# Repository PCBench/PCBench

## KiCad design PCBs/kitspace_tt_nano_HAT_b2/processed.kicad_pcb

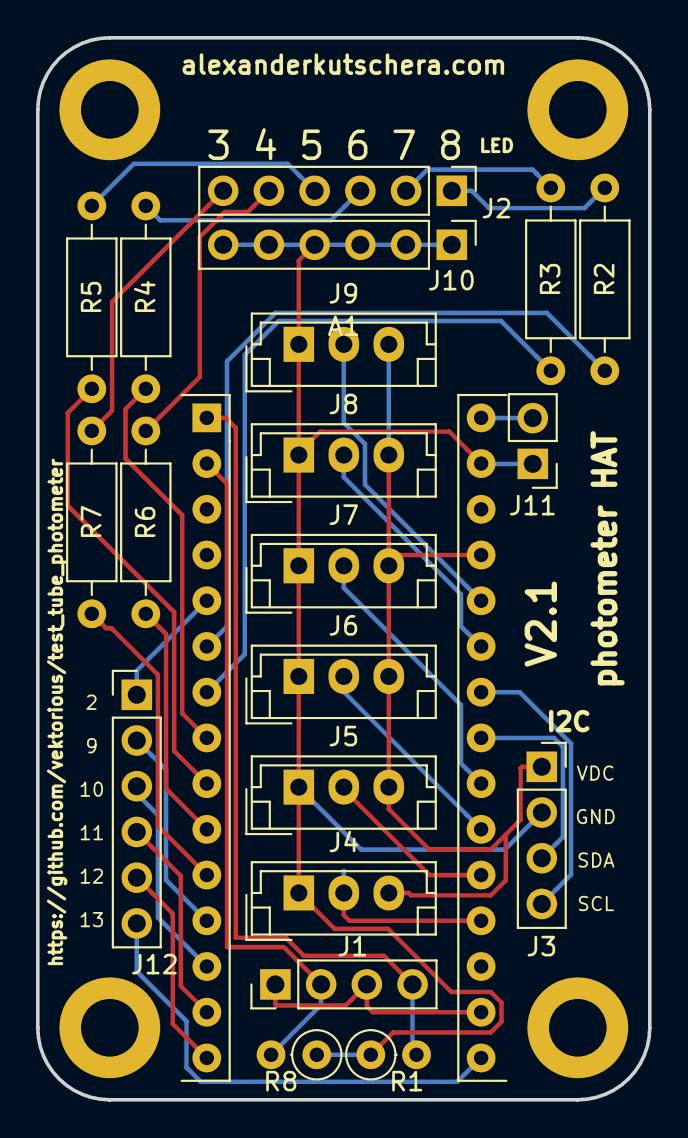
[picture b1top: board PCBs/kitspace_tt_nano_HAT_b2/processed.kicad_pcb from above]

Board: 2 copper layers, 34.0 x 59.0 mm, 21 parts (0 on the bottom side), 32 nets.

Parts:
A1: Arduino_Nano_v3.x; Arduino_Nano2
J1: Conn_01x04_Male; PinHeader_1x04_P2.54mm_Vertical
J2, J10, J12: Conn_01x06_Male; PinHeader_1x06_P2.54mm_Vertical
J3: Conn_01x04_Female; PinSocket_1x04_P2.54mm_Vertical
J4, J5, J6, J7, J8, J9: Conn_01x03_Male; JST_EH_B03B-EH-A_1x03_P2.50mm_Vertical
J11: Conn_01x02_Male; PinHeader_1x02_P2.54mm_Vertical
R1, R8: R; R_Axial_DIN0207_L6.3mm_D2.5mm_P2.54mm_Vertical
R2, R3, R4, R5, R6, R7: R; R_Axial_DIN0207_L6.3mm_D2.5mm_P10.16mm_Horizontal

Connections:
GND: A1.29, J3.2, J4.1, J5.1, J6.1, J7.1, J8.1, J9.1, J10.1, J10.2, J10.3, J10.4, J10.5, J10.6, J11.1, R1.1, R8.1
unnamed: A1.1, J1.4, R1.2
unnamed: A1.2, J1.2, R8.2
unnamed: A1.5, J12.1
unnamed: A1.6, R2.1
unnamed: A1.7, R3.1
unnamed: A1.8, R4.1
unnamed: A1.9, R5.1
unnamed: A1.10, R6.1
unnamed: A1.11, R7.1
unnamed: A1.12, J12.2
unnamed: A1.13, J12.3
unnamed: A1.14, J12.4
unnamed: A1.15, J12.5
unnamed: A1.16, J12.6
unnamed: A1.17, J1.1, J1.3
unnamed: A1.19, J4.2
unnamed: A1.20, J5.2
unnamed: A1.21, J6.2
unnamed: A1.22, J7.2
unnamed: A1.23, J3.3
unnamed: A1.24, J3.4
unnamed: A1.25, J8.2
unnamed: A1.26, J9.2
unnamed: A1.27, J3.1, J4.3, J5.3, J6.3, J7.3, J8.3, J9.3
unnamed: A1.30, J11.2
unnamed: J2.1, R2.2
unnamed: J2.2, R3.2
unnamed: J2.3, R4.2
unnamed: J2.4, R5.2
unnamed: J2.5, R6.2
unnamed: J2.6, R7.2

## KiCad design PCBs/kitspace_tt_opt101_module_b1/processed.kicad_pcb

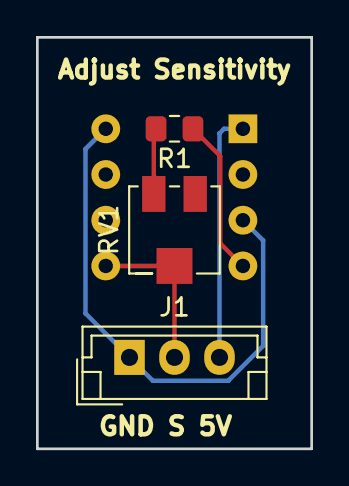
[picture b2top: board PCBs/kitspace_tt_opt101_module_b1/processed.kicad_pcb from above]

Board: 2 copper layers, 15.2 x 22.9 mm, 4 parts (1 on the bottom side), 5 nets.

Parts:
J1: Conn_01x03_Male; JST_EH_B03B-EH-A_1x03_P2.50mm_Vertical
O1: opt101; DIP-8_W7.62mm
R1: R; R_0805_2012Metric_Pad1.15x1.40mm_HandSolder
RV1: R_POT; Potentiometer_Bourns_3214J_Horizontal

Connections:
+5V: J1.3, O1.1
GND: J1.1, O1.3, O1.8
unnamed: J1.2, O1.5, RV1.2
unnamed: O1.4, R1.1
unnamed: R1.2, RV1.1

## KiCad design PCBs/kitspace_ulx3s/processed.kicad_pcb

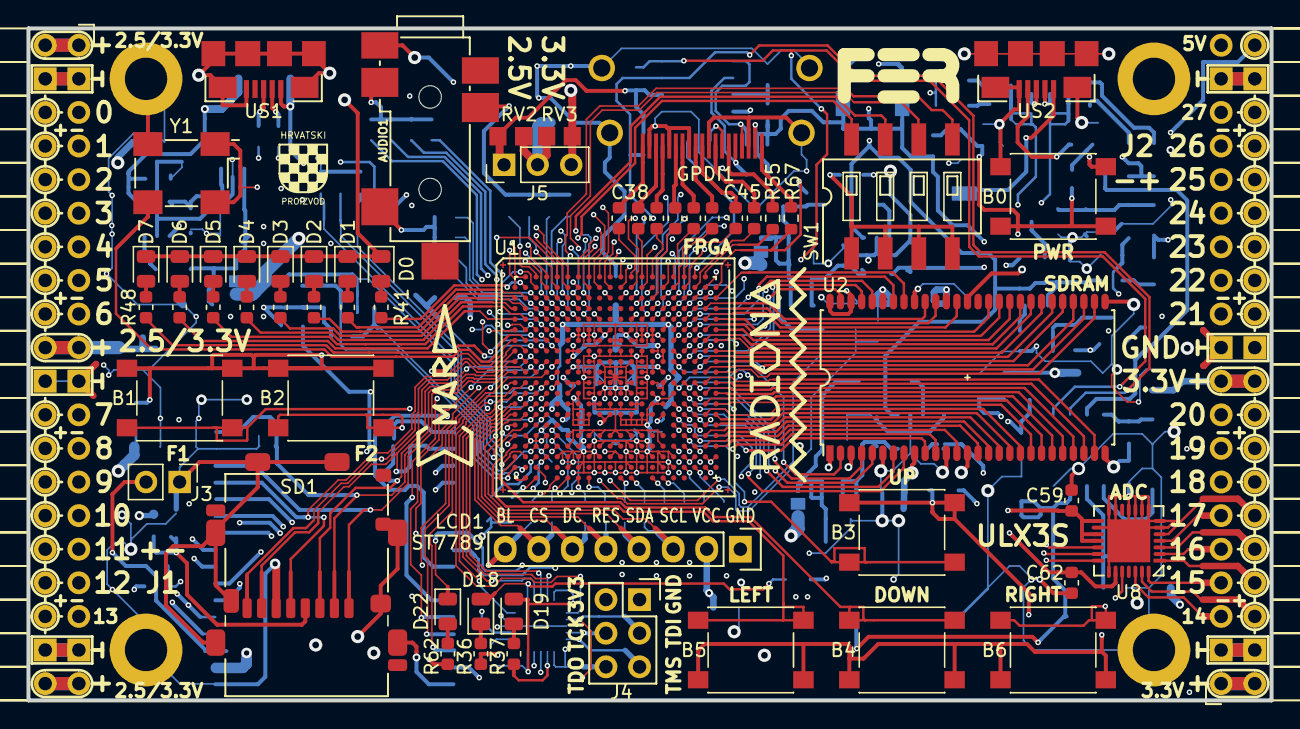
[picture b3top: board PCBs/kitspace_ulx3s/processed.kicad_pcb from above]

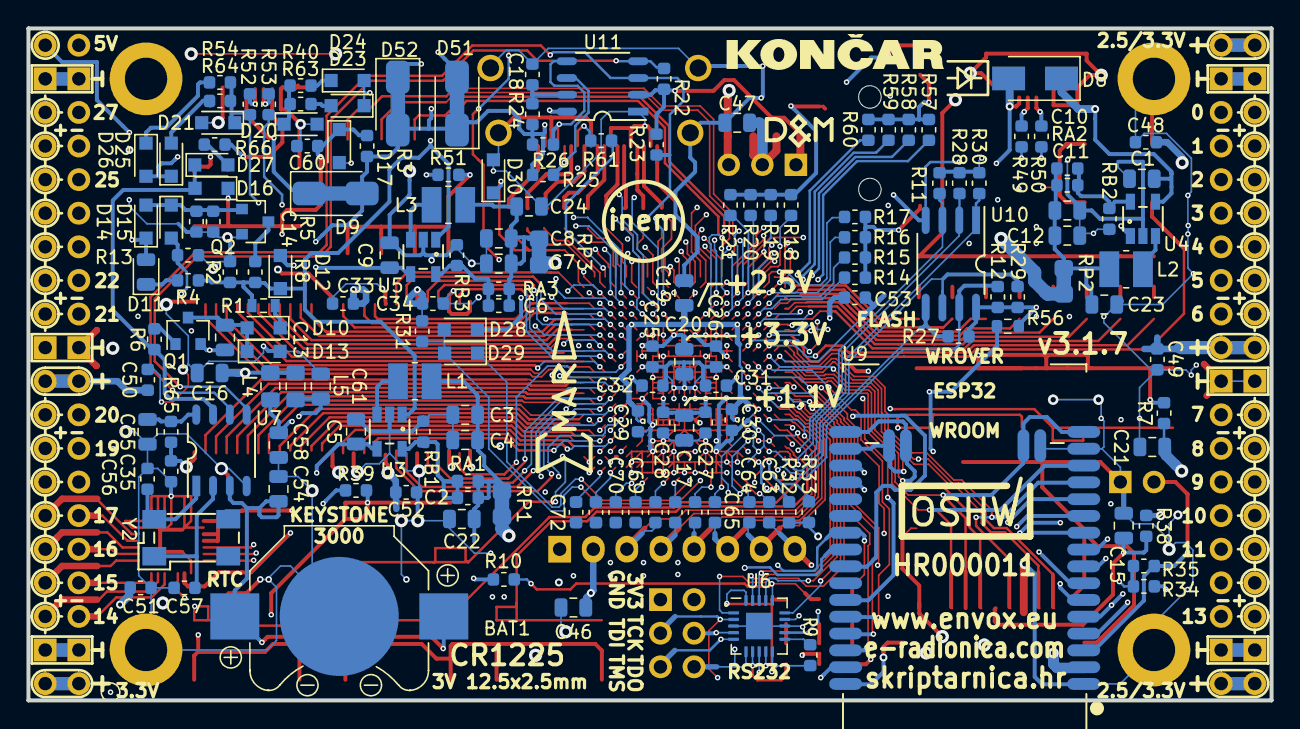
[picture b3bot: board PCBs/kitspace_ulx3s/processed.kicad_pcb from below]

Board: 4 copper layers, 94.0 x 50.8 mm, 234 parts (167 on the bottom side), 287 nets.

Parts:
AE1: 433MHz; TestPoint_Pad_D1.0mm
AUDIO1: JACK_TRS_6PINS; CUI_SJ-43516-SMT
B0, B1, B2, B3, B4, B5, B6: PTS645; SW_SPST_PTS645
BAT1: CR1225; Keystone_3000_1x12mm-CoinCell
C1, C3, C4, C5, C7, C8, C9, C11, C12, C15, C21, C54, C55, C58, C61: 22uF; C_0805_2012Metric
C2, C6, C10, C18: 100pF; C_0603_1608Metric
C13, C16, C17, C19, C20, C22, C23, C24, C46, C47: 2.2uF; C_0805_2012Metric
C14, C59, C60, C62: 220nF; C_0603_1608Metric
C25, C26, C27, C28, C29, C30, C31, C32, C33, C34, C35, C38, C39, C40, C41, C42, C43, C44, C45, C48, C49, C50, C51, C52, C53, C63, C64, C65, C66, C67, C68, C69, C70, C71, C72: 22nF; C_0603_1608Metric
C56, C57: 4.7pF; C_0603_1608Metric
D0, D4, D11, D19: RED; LED_0805_2012Metric
D1, D5: ORANGE; LED_0805_2012Metric
D2, D6, D18: GREEN; LED_0805_2012Metric
D3, D7, D22: BLUE; LED_0805_2012Metric
D8: STPS2L40AF; D_SMA
D9, D51, D52: 0; D_SMA_Jumper_NC
D10, D13, D14, D16, D17, D23, D24, D25, D26, D27, D28, D29: 1N914; D_SOD-323_HandSoldering
D12, D15: BAT54W; D_SOD-323_HandSoldering
D20, D21, D30: 3.6V; D_SOD-323_HandSoldering
D&M: dm2mm
EMARD: emard12mm
EMARD#2: emard12mm
GPDI1: GPDI-D; CONN-10029449-111RLF
H1, H2, H3, H4: HOLE; MountingHole_3.2mm_M3_ISO14580_Pad
HR: HR; hrvatski
J1, J2: CONN_02X20; Socket_Strip_Angled_2x20
J3: WIFI_OFF; PinHeader_1x02_P2.54mm_Vertical
J4: CONN_02X03; Socket_Strip_Straight_2x03
J5: VJ1; PinHeader_1x03_P2.54mm_Vertical
L1, L2, L3: 2.2uH; L_1008_1210
L4, L5: 33uH; L_0805_2012Metric_Pad1.15x1.40mm_HandSolder
LCD1: ST7789; st7789
OSHW: OSHW2mm; oshw
Q1: BC857; SOT-23
Q2: 2N7002; SOT-23
R1, R3, R4, R25, R26, R30: 4.7k; R_0603_1608Metric
R2: 18k; R_0603_1608Metric
R5: 2.2M; R_0603_1608Metric
R6, R8, R14, R18, R29, R40, R54, R57, R66: 1.1k; R_0603_1608Metric
R7, R10, R17, R21, R39, R51, R60: 130; R_0603_1608Metric
R9, R13, R31, R32, R33, R34, R56, R63, R64: 15k; R_0603_1608Metric
R11, R12, R27, R28, R55: 10k; R_0603_1608Metric
R15, R19, R35, R36, R37, R41, R42, R43, R44, R45, R46, R47, R48, R58, R61, R62, R65, R67: 549; R_0603_1608Metric
R16, R20, R59: 270; R_0603_1608Metric
R22, R23: 3.3k; R_0603_1608Metric
R24: 100k; R_0603_1608Metric
R38: 0.47; R_0603_1608Metric
R49, R50, R52, R53: 27; R_0603_1608Metric
RA1, RA2, RA3: 15k; R_0603_1608Metric
RB1: 18k; R_0603_1608Metric
RB2: 4.7k; R_0603_1608Metric
RB3: 3.3k; R_0603_1608Metric
RP1, RP2, RP3: 0; R_0805_2012Metric_Pad1.29x1.40mm_HandSolder_Jumper_NC
RV2, RV3: 0; R_0805_2012Metric_Pad1.29x1.40mm_HandSolder
SD1: 104031-0811; SCHD3A100-104031-0811
SW1: SW_DIP_x04; SW_DIP_x4_W8.61mm_Slide_LowProfile
U1: LFE5U-85F-6BG381C; BGA-381_pitch0.8mm_dia0.4mm
U2: MT48LC16M16A2TG; TSOP54
U3, U4, U5: TLV62569DBV; TSOT-25
U6: FT231XQ; FT231X-QFN-20-1EP_4x4mm_P0.5mm_EP2x2mm
U7: MCP7940NT; SOT96-1
U8: MAX11125; MAX1112x-TQFN-28-1EP_5x5mm_Pitch0.5mm
U9: ESP32
U10: IS25LP128F-JBLE; SOA008-150-208mil
U11: PCA9306D; SM8
US1, US2: MICRO_USB; USB-MICRO-B-FCI-10118192-0001LF
Y1: FNETHE025; Crystal_SMD_7050_4Pads
Y2: 32768Hz; Crystal_SMD_ABS07
fer: fer; fer4mm6
koncar: koncar
radiona: radiona

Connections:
2V5_3V3: C26.1, C47.1, C48.1, C49.1, C53.1, J1.1, J1.2, J1.19, J1.20, J1.39, J1.40, J5.2, R51.1, RV2.2, RV3.1, U1.F9, U1.F10, U1.H6, U1.H7, U1.J6
+1V1: C17.1, C27.1, C28.1, RP1.2, U1.H8, U1.H9, U1.H10, U1.H11, U1.H12, U1.H13, U1.J8, U1.J13, U1.K8, U1.K13, U1.L8, U1.L13, U1.M8, U1.M13, U1.N8, U1.N9, U1.N10, U1.N11, U1.N12, U1.N13, U1.T6, U1.T7, U1.T8, U1.T9, U1.T10, U1.T11, U1.T12, U1.T13, U1.T14, U1.T15, U1.U6, U1.U15
+2V5: C19.1, C29.1, C30.1, J5.1, R22.1, R23.1, RP2.2, RV2.1, U1.F6, U1.F15, U1.P6, U1.P15, U1.V10, U1.V11, U1.V17, U1.V18, U11.2
+3V3: C16.1, C20.1, C21.1, C25.1, C31.1, C32.1, C33.1, C34.1, C35.1, C46.1, C50.1, C51.1, C52.1, D11.2, D14.1, J2.1, J2.2, J2.19, J2.20, J4.2, J5.3, L4.1, L5.1, LCD1.2, R7.1, R11.1, R12.1, R27.1, R28.1, R29.1, R30.1, R31.1, R32.1, R33.1, R34.1, R38.2, R39.1, R56.1, R62.2, R65.1, RP3.2, RV3.2, U1.F11, U1.F12, U1.H14, U1.H15, U1.J15, U1.L6, U1.L7, U1.L14, U1.L15, U1.M6, U1.M15, U1.P9, U1.P10, U1.T2, U1.T3, U1.T4, U1.U2, U2.1, U2.3, U2.9, U2.14, U2.27, U2.43, U2.49, U9.2, U10.8, U11.8, Y1.1, Y1.4
+5V: C1.1, C5.1, C9.1, C13.1, D8.1, D9.2, D51.1, D52.2, GPDI1.18, Q1.2, R3.1, R24.1, R25.1, R26.1, U3.4, U4.4, U5.4
/analog/ADC3V3: C58.1, C59.1, L4.2, U8.15, U8.17, U8.18
/analog/ADCD3V3: C61.1, C62.1, L5.2, U8.23
/analog/AUDIO_L: AUDIO1.2, R14.2, R15.2, R16.2, R17.2
/analog/AUDIO_R: AUDIO1.3, R18.2, R19.2, R20.2, R21.2
/analog/AUDIO_V: AUDIO1.4, R57.2, R58.2, R59.2, R60.2
/blinkey/ALED0: D0.2, R41.2
/blinkey/ALED1: D1.2, R42.2
/blinkey/ALED2: D2.2, R43.2
/blinkey/ALED3: D3.2, R44.2
/blinkey/ALED4: D4.2, R45.2
/blinkey/ALED5: D5.2, R46.2
/blinkey/ALED6: D6.2, R47.2
/blinkey/ALED7: D7.2, R48.2
/blinkey/BTNPUL: B1.1, B2.1, R7.2
/blinkey/BTNPUR: B3.1, B4.1, B5.1, B6.1, R39.2
/blinkey/LED_PWREN: D18.1, R36.1
/blinkey/LED_TXLED: D19.1, R37.2
/blinkey/LED_WIFI: D22.2, R62.1
/blinkey/SWPU: R51.2, SW1.1, SW1.2, SW1.3, SW1.4
/flash/FLASH_MISO: R28.2, U1.V2, U10.2
/flash/FLASH_MOSI: R27.2, U1.W2, U10.5
/flash/FLASH_SCK: R29.2, U1.U3, U10.6
/flash/FLASH_nCS: R30.2, U1.R2, U10.1
/flash/FLASH_nHOLD: R12.2, U1.W1, U10.7
/flash/FLASH_nWP: R11.2, U1.Y2, U10.3
/flash/FPGA_DONE: R32.2, U1.Y3
/flash/FPGA_INITN: R33.2, U1.V3
/flash/FPGA_PROGRAMN: D28.2, D29.2, R31.2, U1.W3
/gpdi/GPDI_CEC: GPDI1.13, R61.1
/gpdi/GPDI_CLK+: C44.2, GPDI1.10
/gpdi/GPDI_CLK-: C45.2, GPDI1.12
/gpdi/GPDI_D0+: C42.2, GPDI1.7
/gpdi/GPDI_D0-: C43.2, GPDI1.9
/gpdi/GPDI_D1+: C40.2, GPDI1.4
/gpdi/GPDI_D1-: C41.2, GPDI1.6
/gpdi/GPDI_D2+: C38.2, GPDI1.1
/gpdi/GPDI_D2-: C39.2, GPDI1.3
/gpdi/GPDI_HPD: GPDI1.19, R67.2
/gpdi/GPDI_UTIL: GPDI1.14, R55.2
/gpdi/VREF2: C18.1, R24.2, U11.7
/gpio/IN5V: D51.2, J2.39
/gpio/OUT5V: D52.1, J2.40
/power/FB1: C2.2, RA1.2, RB1.2, U3.5
/power/FB2: C10.2, RA2.2, RB2.2, U4.5
/power/FB3: C6.2, RA3.2, RB3.2, U5.5
/power/FTDI_nSUSPEND: D12.2, R10.1
/power/HOLD: D11.1, R4.1
/power/L1: L1.1, U3.3
/power/L2: L2.1, U4.3
/power/L3: L3.1, U5.3
/power/OSCI_32k: C56.2, U7.1, Y2.4
/power/OSCO_32k: C57.2, U7.2, Y2.1
/power/P1V1: C2.1, C3.1, C4.1, C22.1, L1.2, RA1.1, RP1.1
/power/P2V5: C10.1, C11.1, C12.1, C23.1, L2.2, RA2.1, RP2.1
/power/P3V3: C6.1, C7.1, C8.1, C24.1, L3.2, RA3.1, RP3.1
/power/PWREN: D12.1, R1.2, R2.1, R4.2, R8.1, U3.1, U4.1, U5.1
/power/RTCVDD: C55.1, R65.2, U7.8
/power/SHD: Q2.3, R8.2
/power/SHUT: C14.1, D14.2, D15.1, Q2.1, R5.1
/power/VBAT: BAT1.1, C54.1, U7.3
/power/WAKE: D10.1, R1.1
/power/WAKEUPn: D16.2, D27.1, R6.2, U7.7
/power/WKUP: C13.2, D10.2, D13.1, Q1.3
/power/WKn: Q1.1, R6.1
/serdes/SRCLKN: C68.1, U1.Y12
/serdes/SRCLKP: C67.2, U1.Y11
/serdes/SRXN00: C64.1, U1.Y6
/serdes/SRXN01: C66.1, U1.Y8
/serdes/SRXN10: C70.1, U1.Y15
/serdes/SRXP00: C63.2, U1.Y5
/serdes/SRXP01: C65.2, U1.Y7
/serdes/SRXP10: C69.2, U1.Y14
/serdes/STXN11: C72.1, U1.W18
/serdes/STXP11: C71.2, U1.W17
/usb/ANT_433MHz: AE1.1, U1.G1
/usb/FPD+: R53.2, US2.3
/usb/FPD-: R52.2, US2.2
/usb/FTD+: R50.2, US1.3
/usb/FTD-: R49.2, US1.2
/usb/US2VBUS: D9.1, US2.1
/wifi/SD3V3: C15.1, R38.1, SD1.4
/wifi/WIFIEN: J3.2, R35.2, U9.3
ADC_CSn: U1.R17, U8.20
ADC_MISO: U1.U16, U8.24
ADC_MOSI: U1.R16, U8.21
ADC_SCLK: U1.P17, U8.19
AUDIO_L0: R14.1, U1.E4
AUDIO_L1: R15.1, U1.D3
AUDIO_L2: R16.1, U1.C3
AUDIO_L3: R17.1, U1.B3
AUDIO_R0: R18.1, U1.A3
AUDIO_R1: R19.1, U1.B5
AUDIO_R2: R20.1, U1.D5
AUDIO_R3: R21.1, U1.C5
AUDIO_V0: R57.1, U1.H5
AUDIO_V1: R58.1, U1.F2
AUDIO_V2: R59.1, U1.F5
AUDIO_V3: R60.1, U1.E5
BTN_D: B4.2, U1.V1
BTN_F1: B1.2, U1.R1
BTN_F2: B2.2, U1.T1
BTN_L: B5.2, U1.U1
BTN_PWRn: D17.2, U1.D6
BTN_R: B6.2, U1.H16
BTN_U: B3.2, U1.R18
CLK_25MHz: U1.G2, Y1.3
FPDI_CEC: R61.2, U1.A18
FPDI_CLK+: C44.1, U1.A17
FPDI_CLK-: C45.1, U1.B18
FPDI_D0+: C42.1, U1.A16
FPDI_D0-: C43.1, U1.B16
FPDI_D1+: C40.1, U1.A14
FPDI_D1-: C41.1, U1.C14
FPDI_D2+: C38.1, U1.A12
FPDI_D2-: C39.1, U1.A13
FPDI_HPD: D30.1, R67.1, U1.B20
FPDI_SCL: R23.2, U1.E12, U7.6, U11.3
FPDI_SDA: R22.2, U1.B19, U7.5, U11.4
FPDI_UTIL: R55.1, U1.A19
FT2V5: D19.2, R9.2, U6.10, U6.20
FTDI_RXD: U1.L4, U6.1
FTDI_TXD: U1.M1, U6.17
FTDI_TXDEN: U1.L3, U6.15
FTDI_nDTR: U1.N1, U6.18
FTDI_nRTS: U1.M3, U6.19
FTDI_nRXLED: U1.L5, U6.14
FTDI_nSLEEP: D18.2, R10.2, U6.16
FTDI_nTXLED: R37.1, U6.7
GN0: J1.5, U1.C11
GN1: J1.7, U1.A11
GN2: J1.9, U1.B10
GN3: J1.11, U1.C10
GN4: J1.13, U1.A8
GN5: J1.15, U1.B8
GN6: J1.17, U1.C7
GN7: J1.23, U1.B6
GN8: J1.25, U1.A5
GN9: J1.27, U1.B1
GN10: J1.29, U1.B4
GN11: J1.31, U1.E3
GN12: J1.33, U1.F3, U9.8
GN13: J1.35, U1.G5, U9.5
GN14: J2.5, U1.U17, U8.26
GN15: J2.7, U1.P16, U8.28
GN16: J2.9, U1.M17, U8.2
GN17: J2.11, U1.L17, U8.4
GN18: J2.13, U1.H17
GN19: J2.15, U1.G18
GN20: J2.17, U1.E17
GN21: J2.23, U1.D17
GN22: J2.25, U1.C15
GN23: J2.27, U1.C17
GN24: J2.29, U1.D16
GN25: J2.31, U1.E14
GN26: J2.33, U1.C13
GN27: J2.35, U1.E13
GND: AUDIO1.1, B0.2, BAT1.2, C1.2, C3.2, C4.2, C5.2, C7.2, C8.2, C9.2, C11.2, C12.2, C14.2, C15.2, C16.2, C17.2, C18.2, C19.2, C20.2, C21.2, C22.2, C23.2, C24.2, C25.2, C26.2, C27.2, C28.2, C29.2, C30.2, C31.2, C32.2, C33.2, C34.2, C35.2, C46.2, C47.2, C48.2, C49.2, C50.2, C51.2, C52.2, C53.2, C54.2, C55.2, C56.1, C57.1, C58.2, C59.2, C60.2, C61.2, C62.2, D0.1, D1.1, D2.1, D3.1, D4.1, D5.1, D6.1, D7.1, D13.2, D20.2, D21.2, D30.2, GPDI1.0, GPDI1.2, GPDI1.5, GPDI1.8, GPDI1.11, GPDI1.17, H1.1, H2.1, H3.1, H4.1, J1.3, J1.4, J1.21, J1.22, J1.37, J1.38, J2.3, J2.4, J2.21, J2.22, J2.37, J2.38, J3.1, J4.1, LCD1.1, Q2.2, R2.2, R5.2, R13.2, R36.2, RB1.1, RB2.1, RB3.1, SD1.6, SD1.GM1, SD1.GM2, SD1.GM3, SD1.GM4, SD1.GS1, SD1.GS2, SD1.GS3, SD1.GS4, U1.B7, U1.B14, U1.C19, U1.D4, U1.F7, U1.F8, U1.F13, U1.F14, U1.G4, U1.G6, U1.G7, U1.G8, U1.G9, U1.G10, U1.G11, U1.G12, U1.G13, U1.G14, U1.G15, U1.G17, U1.H19, U1.J2, U1.J7, U1.J9, U1.J10, U1.J11, U1.J12, U1.J14, U1.K6, U1.K7, U1.K9, U1.K10, U1.K11, U1.K12, U1.K14, U1.K15, U1.L9, U1.L10, U1.L11, U1.L12, U1.M2, U1.M7, U1.M9, U1.M10, U1.M11, U1.M12, U1.M14, U1.M16, U1.N6, U1.N7, U1.N14, U1.N15, U1.P7, U1.P8, U1.P11, U1.P12, U1.P13, U1.P14, U1.R4, U1.R19, U1.U4, U1.U7, U1.U8, U1.U9, U1.U10, U1.U11, U1.U12, U1.U13, U1.U14, U1.V5, U1.V6, U1.V7, U1.V8, U1.V9, U1.V12, U1.V13, U1.V14, U1.V15, U1.V16, U1.V19, U1.V20, U1.W6, U1.W7, U1.W12, U1.W15, U1.W16, U1.W19, U2.6, U2.12, U2.28, U2.41, U2.46, U2.52, U2.54, U3.2, U4.2, U5.2, U6.3, U6.13, U6.21, U7.4, U8.6, U8.7, U8.8, U8.9, U8.10, U8.11, U8.13, U8.14, U8.16, U8.22, U8.29, U9.1, U9.15, U9.38, U10.4, U11.1, US1.5, US1.6, US2.5, US2.6, Y1.2
GP0: J1.6, U1.B11
GP1: J1.8, U1.A10
GP2: J1.10, U1.A9
GP3: J1.12, U1.B9
GP4: J1.14, U1.A7
GP5: J1.16, U1.C8
GP6: J1.18, U1.C6
GP7: J1.24, U1.A6
GP8: J1.26, U1.A4
GP9: J1.28, U1.A2
GP10: J1.30, U1.C4
GP11: J1.32, U1.F4
GP12: J1.34, U1.G3, U9.9
GP13: J1.36, U1.H4, U9.4
GP14: J2.6, U1.U18, U8.27
GP15: J2.8, U1.N17, U8.1
GP16: J2.10, U1.N16, U8.3
GP17: J2.12, U1.L16, U8.5
GP18: J2.14, U1.H18
GP19: J2.16, U1.F17
GP20: J2.18, U1.D18
GP21: J2.24, U1.C18
GP22: J2.26, U1.B15
GP23: J2.28, U1.B17
GP24: J2.30, U1.C16
GP25: J2.32, U1.D14
GP26: J2.34, U1.B13
GP27: J2.36, U1.D13
GPDI_SCL: GPDI1.15, R25.2, U11.6
GPDI_SDA: GPDI1.16, R26.2, U11.5
JTAG_TCK: J4.4, U1.T5, U6.4, U9.30
JTAG_TDI: J4.3, U1.R5, U6.2, U9.37
JTAG_TDO: J4.6, U1.V4, U6.6, U9.6
JTAG_TMS: D22.1, J4.5, U1.U5, U6.5, U9.29
LED0: R41.1, U1.B2
LED1: R42.1, U1.C2
LED2: R43.1, U1.C1
LED3: R44.1, U1.D2
LED4: R45.1, U1.D1
LED5: R46.1, U1.E2
LED6: R47.1, U1.E1
LED7: R48.1, U1.H3
unnamed: D23.2, R63.1
unnamed: D24.1, R40.1
unnamed: D25.2, R64.1
unnamed: D26.1, R54.2
unnamed: D27.2, R66.2
OLED_BL: C63.1, LCD1.8, U1.J4
OLED_CLK: C68.2, LCD1.3, U1.P4
OLED_CS: C64.2, LCD1.7, U1.N2
OLED_DC: C65.1, LCD1.6, U1.P1
OLED_MOSI: C67.1, LCD1.4, U1.P3
OLED_RES: C66.2, LCD1.5, U1.P2
PWRBTn: B0.1, C60.1, D16.1, D17.1, D28.1, R3.2
SDRAM_A0: U1.M20, U2.23
SDRAM_A1: U1.M19, U2.24
SDRAM_A2: U1.L20, U2.25
SDRAM_A3: U1.L19, U2.26
SDRAM_A4: U1.K20, U2.29
SDRAM_A5: U1.K19, U2.30
SDRAM_A6: U1.K18, U2.31
SDRAM_A7: U1.J20, U2.32
SDRAM_A8: U1.J19, U2.33
SDRAM_A9: U1.H20, U2.34
SDRAM_A10: U1.N19, U2.22
SDRAM_A11: U1.G20, U2.35
SDRAM_A12: U1.G19, U2.36
SDRAM_BA0: U1.P19, U2.20
SDRAM_BA1: U1.N20, U2.21
SDRAM_CKE: U1.F20, U2.37
SDRAM_CLK: U1.F19, U2.38
SDRAM_D0: U1.J16, U2.2
SDRAM_D1: U1.L18, U2.4
SDRAM_D2: U1.M18, U2.5
SDRAM_D3: U1.N18, U2.7
SDRAM_D4: U1.P18, U2.8
SDRAM_D5: U1.T18, U2.10
SDRAM_D6: U1.T17, U2.11
SDRAM_D7: U1.U20, U2.13
SDRAM_D8: U1.E19, U2.42
SDRAM_D9: U1.D20, U2.44
SDRAM_D10: U1.D19, U2.45
SDRAM_D11: U1.C20, U2.47
SDRAM_D12: U1.E18, U2.48
SDRAM_D13: U1.F18, U2.50
SDRAM_D14: U1.J18, U2.51
SDRAM_D15: U1.J17, U2.53
SDRAM_DQM0: U1.U19, U2.15
SDRAM_DQM1: U1.E20, U2.39
SDRAM_nCAS: U1.T19, U2.17
SDRAM_nCS: U1.P20, U2.19
SDRAM_nRAS: U1.R20, U2.18
SDRAM_nWE: U1.T20, U2.16
SD_CLK: SD1.5, U1.H2, U9.13
SD_CMD: SD1.3, U1.J1, U9.23
SD_D0: SD1.7, U1.J3, U9.24
SD_D1: SD1.8, U1.H1, U9.26
SD_D2: SD1.1, U1.K1, U9.14
SD_D3: SD1.2, U1.K2, U9.16
SHUTDOWN: D15.2, R13.1, U1.G16
SW1: SW1.8, U1.E8
SW2: SW1.7, U1.D8
SW3: SW1.6, U1.D7
SW4: SW1.5, U1.E7
US2_ID: R66.1, US2.4
USB5V: D8.2, U6.12, US1.1
USB_FPGA_D+: D20.1, R40.2, R53.1, R63.2, U1.D15, U1.E16
USB_FPGA_D-: D21.1, R52.1, R54.1, R64.2, U1.E15, U1.F16
USB_FPGA_PULL_D+: D23.1, D24.2, U1.B12
USB_FPGA_PULL_D-: D25.1, D26.2, U1.C12
USB_FTDI_D+: R50.1, U6.8
USB_FTDI_D-: R49.1, U6.9
USER_PROGRAMN: D29.1, U1.M4
WIFI_EN: R34.2, R35.1, U1.J5
WIFI_GPIO0: R56.2, U1.F1, U9.25
WIFI_GPIO19: U1.N4, U9.31
WIFI_GPIO21: U1.K5, U9.33
WIFI_GPIO22: U1.L2, U9.36
WIFI_GPIO25: U1.E9, U9.10
WIFI_GPIO26: U1.L1, U9.11
WIFI_GPIO27: U1.N3, U9.12
WIFI_GPIO35: U1.E6, U9.7
WIFI_RXD: U1.K3, U9.34
WIFI_TXD: U1.K4, U9.35
nRESET: R9.1, U6.11

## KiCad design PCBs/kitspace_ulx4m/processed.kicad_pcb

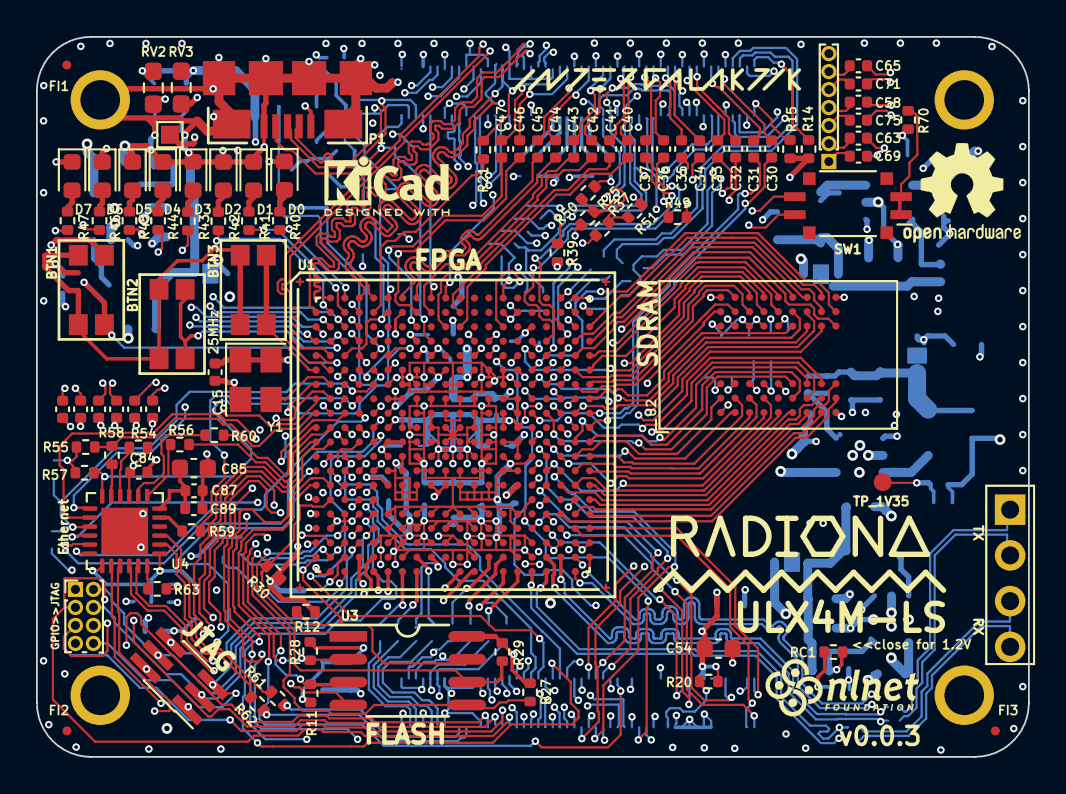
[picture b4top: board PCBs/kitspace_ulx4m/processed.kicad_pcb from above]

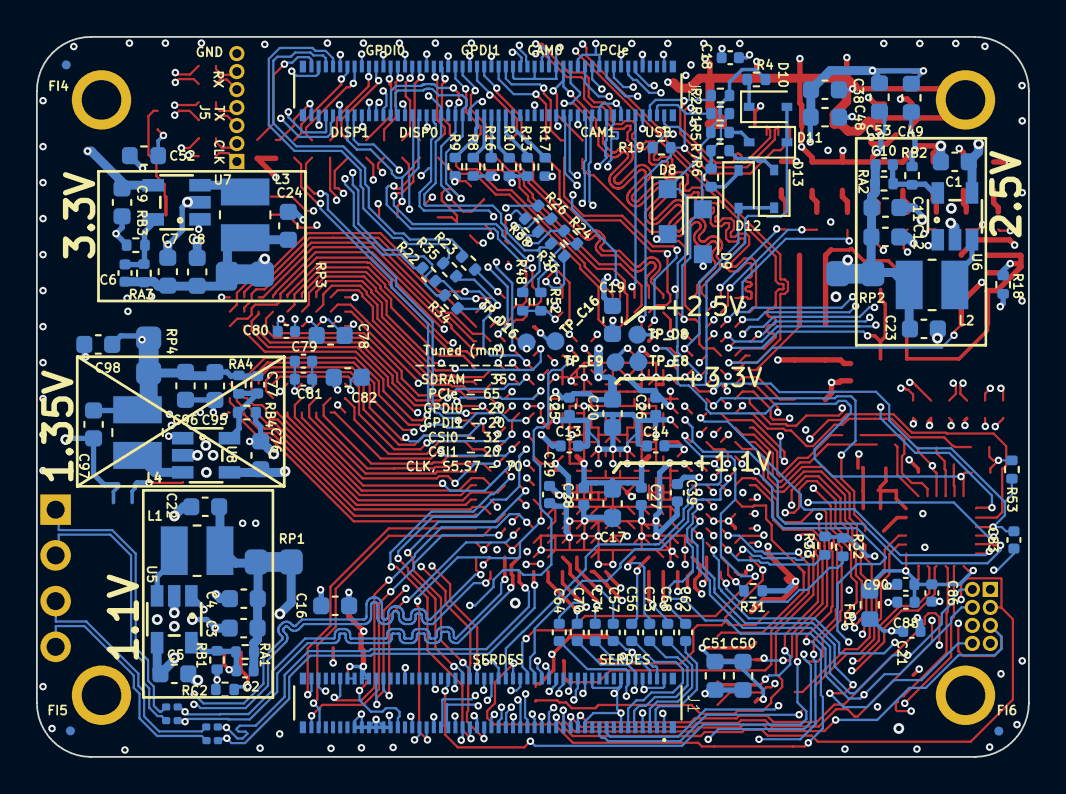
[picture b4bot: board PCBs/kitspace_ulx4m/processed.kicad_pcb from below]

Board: 6 copper layers, 55.1 x 40.0 mm, 233 parts (129 on the bottom side), 296 nets.

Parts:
1.1V_1: 1.1V; TestPoint_Pad_1.0x1.0mm
BTN1, BTN2, BTN3: SW_Push; Switch_EVPAA
C1, C3, C4, C5, C7, C8, C9, C11, C12, C76, C95, C96: 22uF; C_0603_1608Metric
C2, C6, C10, C77: 100pF; C_0402_1005Metric
C13, C14, C15, C18, C21, C25, C26, C27, C28, C29, C39, C79, C80, C81: 22nF; C_0402_1005Metric
C16, C17, C19, C20, C22, C23, C24, C38, C54, C78, C97, C98: 2.2uF; C_0603_1608Metric
C30, C31, C32, C33, C34, C35, C36, C37, C40, C41, C42, C43, C44, C45, C46, C47, C83, C84, C90: 100n; C_0402_1005Metric
C48, C49, C50, C51, C52, C53, C82: 22nF; C_0603_1608Metric
C55, C56, C57, C58, C59, C61, C62, C63, C64, C65, C66, C67, C68, C69, C70, C71, C72, C73, C74, C75, C88: 22n; C_0402_1005Metric
C85: 1u1R; C_0603_1608Metric
C86, C89: 10n; C_0402_1005Metric
C87: 470p; C_0402_1005Metric
C91, C92, C93, C94: 22n; C_0201_0603Metric
D0, D4: RED; LED_0603_1608Metric
D1, D5: ORANGE; LED_0603_1608Metric
D2, D6: GREEN; LED_0603_1608Metric
D3, D7: BLUE; LED_0603_1608Metric
D8, D9: 3.6V; D_SOD-323_HandSoldering
D10, D11, D12, D13: 1N914; D_SOD-323
FB1: 30R; L_0603_1608Metric
FI1, FI2, FI3, FI4, FI5, FI6: Fi; Fiducial_0.5mm_Mask1mm
H1, H2, H3, H4: HOLE; MountingHole_3.2mm_M3_ISO14580_Pad
J1, J2: DF40C-100DP-0.4V(51); HRS_DF40C-100DP-0.4V(51)
J3: JTAG; PinHeader_2x03_P1.00mm_Vertical_SMD
J4: Antenna; PinHeader_1x04_P2.54mm_Vertical
J5: SerDes; PinHeader_1x07_P1.00mm_Vertical
J6: GPIO>>JTAG; PinHeader_2x04_P1.00mm_Vertical
L1, L2, L3, L4: 2.2uH; L_1008_1210
P1: USB_OTG; USB-MICRO-B-FCI-10118192-0001LF
R1, R2: 27R; R_0402_1005Metric
R4, R6, R29: 1k; R_0402_1005Metric
R5, R7, R8, R9, R11, R12, R16, R17, R27, R28, R31, R32, R33: 15k; R_0402_1005Metric
R10, R13, R14, R15, R19, R20, R30: 4k7; R_0402_1005Metric
R18, R21, R22, R23, R24, R25, R26, R34, R35, R36, R37, R38, R40, R41, R42, R43, R44, R45, R46, R47, R61, R62, R70: 300; R_0402_1005Metric
R39, R48, R49, R50, R51, R52: 70; R_0402_1005Metric
R53: 10K; R_0402_1005Metric
R54, R56, R58, R60: 10R; R_0402_1005Metric
R55, R57: 1K5; R_0402_1005Metric
R59: 33R; R_0402_1005Metric
R63: 12K1; R_0402_1005Metric
RA1, RA2, RA3, RA4: 15k; R_0402_1005Metric
RB1: 18k; R_0402_1005Metric
RB2: 4k7; R_0402_1005Metric
RB3: 3k3; R_0402_1005Metric
RB4: 12k; R_0402_1005Metric
RC1: *DNP; R_0402_1005Metric
RC2: 91k; R_0402_1005Metric
RP1, RP2, RP3, RP4: 0; R_0805_2012Metric_Pad1.29x1.40mm_HandSolder_Jumper_NC
RV2, RV3: 0; R_0603_1608Metric_Pad0.98x0.95mm_HandSolder
SW1: SW_DIP_x02; SW_DIP_SPSTx02_Slide_Copal_CVS-02xB_W5.9mm_P1mm
TP_1V35: 1V35; Testpoint_smd_1mm
TP_C16: C16; Testpoint_smd_1mm
TP_D8: D8; Testpoint_smd_1mm
TP_D16: D16; Testpoint_smd_1mm
TP_E8: E8; Testpoint_smd_1mm
TP_E9: E9; Testpoint_smd_1mm
U1: LFE5U-85F-6BG381C; BGA-381_pitch0.8mm_dia0.4mm
U2: IS42S16320D-6BLI
U3: IS25LP128F-JBLE; SOA008-150-208mil
U4: LAN8720A; QFN-24-1EP_4x4mm_P0.5mm_EP2.6x2.6mm
U5, U6, U7, U8: TLV62569DBV; TSOT-25
Y1: FNETHE025; Crystal_SMD_TXC_7M-4Pin_3.2x2.5mm
radiona: radiona

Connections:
2V5_3V3: C26.1, C38.1, C48.1, C49.1, C53.1, RV2.2, RV3.1, U1.F9, U1.F10, U1.H6, U1.H7, U1.J6
+1V1: 1.1V_1.1, C17.1, C27.1, C28.1, RP1.2, U1.H8, U1.H9, U1.H10, U1.H11, U1.H12, U1.H13, U1.J8, U1.J13, U1.K8, U1.K13, U1.L8, U1.L13, U1.M8, U1.M13, U1.N8, U1.N9, U1.N10, U1.N11, U1.N12, U1.N13, U1.T6, U1.T7, U1.T8, U1.T9, U1.T10, U1.T11, U1.T12, U1.T13, U1.T14, U1.T15, U1.U6, U1.U15
+1V35: C98.1, RP4.2, TP_1V35.1
+2V5: C19.1, C29.1, C39.1, RP2.2, RV2.1, U1.F6, U1.F15, U1.P6, U1.P15, U1.V10, U1.V11, U1.V17, U1.V18
+3.3VA: C86.1, C88.1, C90.1, FB1.2, U4.1, U4.19
+5V: C1.1, C5.1, C9.1, C76.1, J1.77, J1.79, J1.81, J1.83, J1.85, J1.87, P1.1, R10.1, R13.1, R14.1, R15.1, U5.1, U5.4, U6.1, U6.4, U7.1, U7.4, U8.1, U8.4
/blinkey/ALED0: D0.2, R40.2
/blinkey/ALED1: D1.2, R41.2
/blinkey/ALED2: D2.2, R42.2
/blinkey/ALED3: D3.2, R43.2
/blinkey/ALED4: D4.2, R44.2
/blinkey/ALED5: D5.2, R45.2
/blinkey/ALED6: D6.2, R46.2
/blinkey/ALED7: D7.2, R47.2
/ethernet/ACTLED: R61.2, U4.3
/ethernet/LINKLED: R62.2, U4.2
/ethernet/RBIAS: R63.1, U4.24
/ethernet/VDDCR: C85.1, C87.1, C89.1, U4.6
/ethernet/XTAL: R59.1, U4.5
/flash/FLASH_MISO: R28.2, U1.V2, U3.2
/flash/FLASH_MOSI: R27.2, U1.W2, U3.5
/flash/FLASH_SCK: R29.2, U1.U3, U3.6
/flash/FLASH_nCS: R30.2, U1.R2, U3.1
/flash/FLASH_nHOLD: R12.2, U1.W1, U3.7
/flash/FLASH_nWP: R11.2, U1.Y2, U3.3
/flash/FPGA_DONE: R32.2, U1.Y3
/flash/FPGA_INITN: R33.2, U1.V3
/flash/FPGA_PROGRAMN: R31.2, U1.W3
/gpio/CAM0_D0_LP: R21.2, U1.B5
/power/FB1: C2.2, RA1.2, RB1.2, RC1.2, U5.5
/power/FB2: C10.2, RA2.2, RB2.2, U6.5
/power/FB3: C6.2, RA3.2, RB3.2, U7.5
/power/FB4: C77.2, RA4.2, RB4.2, U8.5
/power/L1: L1.1, U5.3
/power/L2: L2.1, U6.3
/power/L3: L3.1, U7.3
/power/L4: L4.1, U8.3
/power/P1V1: C2.1, C3.1, C4.1, C22.1, L1.2, RA1.1, RP1.1
/power/P1V35: C77.1, C95.1, C96.1, C97.1, L4.2, RA4.1, RP4.1
/power/P2V5: C10.1, C11.1, C12.1, C23.1, L2.2, RA2.1, RP2.1
/power/P3V3: C6.1, C7.1, C8.1, C24.1, L3.2, RA3.1, RP3.1
/serdes/1N: C91.1, J4.1
/serdes/1P: C92.1, J4.2
/serdes/2N: C93.1, J4.3
/serdes/2P: C94.1, J4.4
/serdes/CLK_0_N: C66.1, U1.Y12
/serdes/CLK_0_P: C59.2, U1.Y11
/serdes/CLK_1_N: C69.1, U1.W20
/serdes/CLK_1_P: C63.2, U1.Y19
/serdes/S_0_N: C67.1, U1.Y6
/serdes/S_0_P: C61.2, U1.Y5
/serdes/S_1_N: C68.1, U1.Y8
/serdes/S_1_P: C62.2, U1.Y7
/serdes/S_2_N: C72.1, U1.W5
/serdes/S_2_P: C55.2, U1.W4
/serdes/S_3_N: C73.1, U1.W9
/serdes/S_3_P: C56.2, U1.W8
/serdes/S_4_N: C70.1, U1.Y15
/serdes/S_4_P: C64.2, U1.Y14
/serdes/S_5_N: C71.1, C93.2, U1.Y17
/serdes/S_5_P: C65.2, C94.2, U1.Y16
/serdes/S_6_N: C74.1, U1.W14
/serdes/S_6_P: C57.2, U1.W13
/serdes/S_7_N: C75.1, C91.2, U1.W18
/serdes/S_7_P: C58.2, C92.2, U1.W17
BTN1: BTN1.2, U1.E1
BTN2: BTN2.2, U1.D2
BTN3: BTN3.2, U1.F1
CAM0_C_N: J2.40, U1.E2
CAM0_C_P: J2.42, U1.F2
CAM0_D0_N: J2.28, U1.A5
CAM0_D0_P: J2.30, R21.1, U1.A4
CAM0_D1_N: J2.34, U1.B1
CAM0_D1_P: J2.36, U1.A2
CAM1_C_N: J2.27, U1.F3
CAM1_C_P: J2.29, U1.G3
CAM1_D0_N: J2.15, U1.B4
CAM1_D0_P: J2.17, U1.C4
CAM1_D1_N: J2.21, U1.D5
CAM1_D1_P: J2.23, U1.E4
CLK_25MHz: U1.G2, Y1.3
CM4_1.8V: J1.88, J1.90
CM4_3.3V: C13.1, C14.1, C15.1, C16.1, C18.1, C20.1, C21.1, C25.1, C50.1, C51.1, C52.1, C54.1, C78.1, C79.1, C80.1, C81.1, C82.1, C84.1, FB1.1, J1.84, J1.86, J3.2, R8.1, R11.1, R12.1, R16.1, R18.2, R19.2, R20.2, R27.1, R28.1, R29.1, R30.1, R31.1, R32.1, R33.1, R53.1, R54.2, R55.1, R57.1, R70.1, RP3.2, RV3.2, U1.F11, U1.F12, U1.H14, U1.H15, U1.J15, U1.L6, U1.L7, U1.L14, U1.L15, U1.M6, U1.M15, U1.P9, U1.P10, U1.T2, U1.T3, U1.T4, U1.U2, U2.A7, U2.A9, U2.B3, U2.C7, U2.D3, U2.E7, U2.J9, U3.8, U4.9, Y1.1, Y1.4
Camera_GPIO: J1.97, U1.U19
DSI0_C_N: J2.69, J2.87, R38.2, R39.1
DSI0_C_P: J2.71, J2.89, R26.1, R49.1
DSI0_D0_N: J2.57, J2.75, R37.2, R51.1
DSI0_D0_P: J2.59, J2.77, R25.1, R50.1
DSI0_D1_N: J2.63, J2.81, R36.2, R48.1
DSI0_D1_P: J2.65, J2.83, R24.1, R52.1
DSI1_D2_N: J2.93, R34.2
DSI1_D2_P: J2.95, R22.1
DSI1_D3_N: J2.94, R35.2
DSI1_D3_P: J2.96, R23.1
ETH_0N: C70.2, J1.10, U4.20
ETH_0P: C64.1, J1.12, U4.21
ETH_1N: C74.2, J1.6, U4.22
ETH_1P: C57.1, J1.4, U4.23
ETH_2N: C73.2, J1.9
ETH_2P: C56.1, J1.11
ETH_3N: C68.2, J1.5
ETH_3P: C62.1, J1.3
ETH_MDC: U1.J5, U4.13
ETH_MDIO: R57.2, U1.E6, U4.12
ETH_nLED1: J1.19, R62.1
ETH_nLED2: J1.17, R61.1
ETH_~RESET: C83.2, R53.2, U1.G5, U4.15
FPDI_CLK+: C31.1, U1.J20
FPDI_CLK-: C30.1, U1.K20
FPDI_D0+: C33.1, U1.F17
FPDI_D0-: C32.1, U1.G18
FPDI_D1+: C35.1, U1.D18
FPDI_D1-: C34.1, U1.E17
FPDI_D2+: C37.1, U1.C18
FPDI_D2-: C36.1, U1.D17
GLOBAL_EN: J1.99, U1.U18
GN0: C40.1, U1.C11
GN3: C42.1, U1.C10
GN4: C44.1, U1.A8
GN5: C46.1, U1.B8
GND: C1.2, C3.2, C4.2, C5.2, C7.2, C8.2, C9.2, C11.2, C12.2, C13.2, C14.2, C15.2, C16.2, C17.2, C18.2, C19.2, C20.2, C21.2, C22.2, C23.2, C24.2, C25.2, C26.2, C27.2, C28.2, C29.2, C38.2, C39.2, C48.2, C49.2, C50.2, C51.2, C52.2, C53.2, C54.2, C76.2, C78.2, C79.2, C80.2, C81.2, C82.2, C83.1, C84.2, C85.2, C86.2, C87.2, C88.2, C89.2, C90.2, C95.2, C96.2, C97.2, C98.2, D0.1, D1.1, D2.1, D3.1, D4.1, D5.1, D6.1, D7.1, D8.2, D9.2, H1.1, H2.1, H3.1, H4.1, J1.1, J1.2, J1.7, J1.8, J1.13, J1.14, J1.22, J1.23, J1.32, J1.33, J1.42, J1.43, J1.52, J1.53, J1.59, J1.60, J1.65, J1.66, J1.71, J1.74, J1.98, J2.7, J2.8, J2.13, J2.14, J2.19, J2.20, J2.25, J2.26, J2.31, J2.32, J2.37, J2.38, J2.44, J2.50, J2.55, J2.56, J2.61, J2.62, J2.67, J2.68, J2.73, J2.74, J2.79, J2.80, J2.85, J2.86, J2.91, J2.92, J2.97, J2.98, J3.1, J5.7, P1.5, P1.6, R9.1, R17.1, R39.2, R48.2, R49.2, R50.2, R51.2, R52.2, R63.2, RB1.1, RB2.1, RB3.1, RB4.1, RC2.1, U1.B7, U1.B14, U1.C19, U1.D4, U1.F7, U1.F8, U1.F13, U1.F14, U1.G4, U1.G6, U1.G7, U1.G8, U1.G9, U1.G10, U1.G11, U1.G12, U1.G13, U1.G14, U1.G15, U1.G17, U1.H19, U1.J2, U1.J7, U1.J9, U1.J10, U1.J11, U1.J12, U1.J14, U1.K6, U1.K7, U1.K9, U1.K10, U1.K11, U1.K12, U1.K14, U1.K15, U1.L9, U1.L10, U1.L11, U1.L12, U1.M2, U1.M7, U1.M9, U1.M10, U1.M11, U1.M12, U1.M14, U1.M16, U1.N6, U1.N7, U1.N14, U1.N15, U1.P7, U1.P8, U1.P11, U1.P12, U1.P13, U1.P14, U1.R4, U1.R19, U1.U4, U1.U7, U1.U8, U1.U9, U1.U10, U1.U11, U1.U12, U1.U13, U1.U14, U1.V5, U1.V6, U1.V7, U1.V8, U1.V9, U1.V12, U1.V13, U1.V14, U1.V15, U1.V16, U1.V19, U1.V20, U1.W6, U1.W7, U1.W12, U1.W15, U1.W16, U1.W19, U2.A1, U2.A3, U2.B7, U2.C3, U2.D7, U2.E3, U2.J1, U3.4, U4.25, U5.2, U6.2, U7.2, U8.2, Y1.2
GP0: C41.1, U1.B11
GP3: C43.1, U1.B9
GP4: C45.1, U1.A7
GP5: C47.1, U1.C8
GPIO2: J1.58, U1.M17
GPIO3: J1.56, U1.P17
GPIO4: J1.54, U1.P16
GPIO5: J1.34, U1.N1
GPIO6: J1.30, U1.R1
GPIO7: J1.37, U1.P3
GPIO8: J1.39, U1.P4
GPIO9: J1.40, U1.L5
GPIO10: J1.44, U1.K4
GPIO11: J1.38, U1.N2
GPIO12: J1.31, J6.3, U1.L2
GPIO13: J1.28, U1.T1
GPIO14: J1.55, U1.N18
GPIO15: J1.51, U1.N16
GPIO16: J1.29, J6.5, U1.L1
GPIO17: J1.50, U1.H3
GPIO18: J1.49, U1.N5
GPIO19: J1.26, U1.U1
GPIO20: J1.27, J6.1, U1.L3
GPIO21: J1.25, J6.7, U1.L4
GPIO22: J1.46, U1.M3
GPIO23: J1.47, U1.N4
GPIO24: J1.45, U1.N3
GPIO25: J1.41, U1.P5
GPIO26: J1.24, U1.V1
GPIO27: J1.48, U1.R17
HDMI0_CEC: J2.51, R8.2
HDMI0_CLK_N: C30.2, J2.90
HDMI0_CLK_P: C31.2, J2.88
HDMI0_HOTPLUG: J2.53, R9.2
HDMI0_SCL: J2.100, R14.2
HDMI0_SDA: J2.99, R15.2
HDMI0_TX0_N: C32.2, J2.84
HDMI0_TX0_P: C33.2, J2.82
HDMI0_TX1_N: C34.2, J2.78
HDMI0_TX1_P: C35.2, J2.76
HDMI0_TX2_N: C36.2, J2.72
HDMI0_TX2_P: C37.2, J2.70
HDMI1_CEC: J2.49, R16.2
HDMI1_CLK_N: C40.2, J2.66
HDMI1_CLK_P: C41.2, J2.64
HDMI1_HOTPLUG: J2.43, R17.2
HDMI1_SCL: J2.47, R10.2
HDMI1_SDA: J2.45, R13.2
HDMI1_TX0_N: C42.2, J2.60
HDMI1_TX0_P: C43.2, J2.58
HDMI1_TX1_N: C44.2, J2.54
HDMI1_TX1_P: C45.2, J2.52
HDMI1_TX2_N: C46.2, J2.48
HDMI1_TX2_P: C47.2, J2.46
ID_SC: J1.35, U1.J3
ID_SD: J1.36, U1.H1
JTAG_TCK: J3.4, J6.2, U1.T5
JTAG_TDI: J3.3, J6.4, U1.R5
JTAG_TDO: J3.6, J6.6, U1.V4
JTAG_TMS: J3.5, J6.8, U1.U5
LED0: R40.1, U1.A3
LED1: R41.1, U1.B3
LED2: R42.1, U1.B2
LED3: R43.1, U1.C3
LED4: R44.1, U1.C2
LED5: R45.1, U1.C1
LED6: R46.1, U1.D1
LED7: R47.1, U1.D3
unnamed: BTN1.1, BTN2.1, BTN3.1, R18.1
unnamed: D10.1, R4.1
unnamed: D11.2, R5.1
unnamed: D12.1, R6.1
unnamed: D13.2, R7.1
unnamed: R22.2, U1.A19
unnamed: R23.2, U1.A18
unnamed: R24.2, U1.A14
unnamed: R25.2, U1.D13
unnamed: R26.2, U1.D12
unnamed: R34.1, U1.B20
unnamed: R35.1, U1.B19
unnamed: R36.1, U1.C14
unnamed: R37.1, U1.E13
unnamed: R38.1, U1.E12
unnamed: R54.1, U4.10
unnamed: R56.1, U4.7
unnamed: R58.2, U4.11
unnamed: R60.1, U4.8
unnamed: R70.2, SW1.1, SW1.2
unnamed: RC1.1, RC2.2
unnamed: TP_C16.1, U1.C16
unnamed: TP_D8.1, U1.D8
unnamed: TP_D16.1, U1.D16
unnamed: TP_E8.1, U1.E8
unnamed: TP_E9.1, U1.E9
PCIe_CLK_N: C66.2, J2.12
PCIe_CLK_P: C59.1, J2.10
PCIe_CLK_nREQ: J2.2, U1.A10
PCIe_RX_N: C67.2, J2.18
PCIe_RX_P: C61.1, J2.16
PCIe_TX_N: C72.2, J2.24
PCIe_TX_P: C55.1, J2.22
PCIe_nRST: J2.9, U1.A9
RGMII_REF_CLK: U1.H2, U4.14
RGMII_RXD0: R60.2, U1.K1
RGMII_RXD1: R56.2, U1.K2
RGMII_RX_DV: R55.2, R58.1, U1.J1
RGMII_TXD0: U1.K5, U4.17
RGMII_TXD1: U1.J4, U4.18
RGMII_TX_CLK: R59.2, U1.H4
RGMII_TX_EN: U1.K3, U4.16
RUN_PG: J1.92, U1.U16
SCL0: J1.80, U1.U17
SDA0: J1.82, U1.T17
SDRAM_A0: U1.H16, U2.H7
SDRAM_A1: U1.D19, U2.H8
SDRAM_A2: U1.F16, U2.J8
SDRAM_A3: U1.E18, U2.J7
SDRAM_A4: U1.T19, U2.J3
SDRAM_A5: U1.T18, U2.J2
SDRAM_A6: U1.J16, U2.H3
SDRAM_A7: U1.P18, U2.H2
SDRAM_A8: U1.T20, U2.H1
SDRAM_A9: U1.L19, U2.G3
SDRAM_A10: U1.C20, U2.H9
SDRAM_A11: U1.K19, U2.G2
SDRAM_A12: U1.R20, U2.G1
SDRAM_BA0: U1.J19, U2.G7
SDRAM_BA1: U1.L16, U2.G8
SDRAM_CKE: U1.J17, U2.F3
SDRAM_CLK: U1.L20, U2.F2
SDRAM_D0: U1.J18, U2.A8
SDRAM_D1: U1.G20, U2.B9
SDRAM_D2: U1.G19, U2.B8
SDRAM_D3: U1.E16, U2.C9
SDRAM_D4: U1.F19, U2.C8
SDRAM_D5: U1.F20, U2.D9
SDRAM_D6: U1.H18, U2.D8
SDRAM_D7: U1.F18, U2.E9
SDRAM_D8: U1.P19, U2.E1
SDRAM_D9: U1.N17, U2.D2
SDRAM_D10: U1.M18, U2.D1
SDRAM_D11: U1.N20, U2.C2
SDRAM_D12: U1.N19, U2.C1
SDRAM_D13: U1.M20, U2.B2
SDRAM_D14: U1.M19, U2.A2
SDRAM_D15: U1.L17, U2.B1
SDRAM_DQM0: U1.E20, U2.E8
SDRAM_DQM1: U1.P20, U2.F1
SDRAM_nCAS: U1.H20, U2.F7
SDRAM_nCS: U1.D20, U2.G9
SDRAM_nRAS: U1.G16, U2.F8
SDRAM_nWE: U1.E19, U2.F9
SD_CLK: J1.57, U1.G1
SD_CMD: J1.62, U1.P1
SD_D0: J1.63, U1.B15
SD_D1: J1.67, U1.R16
SD_D2: J1.69, U1.E14
SD_D3: J1.61, U1.P2
SD_PWR_ON: J1.75, R20.1, U1.E15
SRCLK1N: C69.2, J5.1
SRCLK1P: C63.1, J5.2
SRX11N: C71.2, J5.5
SRX11P: C65.1, J5.6
STX11N: C75.2, J5.3
STX11P: C58.1, J5.4
SW1: SW1.4, U1.L18
SW2: SW1.3, U1.K18
US2_ID: J2.1, P1.4, R19.1, U1.D9
USB_FPGA_D+: D8.1, R2.2, R4.2, R5.2, U1.A6, U1.F4
USB_FPGA_D-: D9.1, R1.2, R6.2, R7.2, U1.B6, U1.E3
USB_FPGA_PULL_D+: D10.2, D11.1, U1.F5
USB_FPGA_PULL_D-: D12.2, D13.1, U1.E5
USB_N: J2.3, P1.2, R1.1
USB_P: J2.5, P1.3, R2.1
nEXTRST: J1.100, U1.U20

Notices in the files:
PCBs/kitspace_ulx4m/processed.kicad_pcb:
License: CERN-OHL-S v2
